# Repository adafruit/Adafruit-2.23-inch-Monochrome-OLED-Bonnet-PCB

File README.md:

## Adafruit 2.23" Monochrome OLED Bonnet for Raspberry Pi Sensor PCB

<a href="http://www.adafruit.com/products/4567"><br/>
Click here to purchase one from the Adafruit shop</a>

PCB files for the Adafruit 2.23" Monochrome OLED Bonnet for Raspberry Pi Sensor. 

Format is EagleCAD schematic and board layout
* https://www.adafruit.com/product/4567

### Description

If you're looking for a bright, readable OLED display for a [Raspberry Pi](https://www.adafruit.com/category/361) (most likely a [Pi Zero](https://www.adafruit.com/category/813)) project, this might be just the thing you need!

The **Adafruit 2.23" Monochrome OLED Bonnet for Raspberry Pi** is your chonky OLED pal, ready to snap onto any and all Raspberry Pi computers, to give you a vivid display. The Bonnet comes with a 2.13" diagonal monochrome 128x32 OLED, with sharp white pixels. The OLED the I2C pins plus GPIO #4 for reset, so you have plenty of GPIO connections available for buttons, LEDs, sensors, etc. It sits nice and flat so many cases that have an open top can have this display inserted.

[Compared to our similar PiOLED display](https://www.adafruit.com/product/3527), this OLED has the same resolution but is much larger, so it can be read from across the room. This screen is made of 128x32 individual white OLED pixels and because the display makes its own light, no backlight is required. This reduces the power required to run the OLED and is why the display has such high contrast; we really like OLED display for their crispness!

Using the display is very easy, we have a Python library for the SSD1305 chipset. Our example code allows you to draw images, text, whatever you like, using the Python imaging library. Our tests showed 30 FPS update rates so you can do animations or simple video.

**Comes completely pre-assembled and tested** so you don't need to do anything but plug it in and install our Python code! **Works with any Raspberry Pi computer that has a 2x20 connector**, such as the Pi B+, Pi 2, Pi 3, Pi 4, and Pi Zero (and any others that have a 2x20 connector!)

[On the bottom, we have a Qwiic/STEMMA QT connector for I2C sensors and devices so you can plug and play any of our STEMMA QT devices](https://www.adafruit.com/?q=stemma%20qt).

Please note that OLED displays are made of hundreds of...OLEDs! That means each pixel is a little organic LED, and if it's kept on for over 1000 hours it'll start to dim. If you want to keep the display uniformly bright, please turn off the display (set the pixels off) when it isn't needed to keep them from dimming.

### License

Adafruit invests time and resources providing this open source design, please support Adafruit and open-source hardware by purchasing products from [Adafruit](https://www.adafruit.com)!

Designed by Limor Fried/Ladyada for Adafruit Industries.

Creative Commons Attribution/Share-Alike, all text above must be included in any redistribution. 
See license.txt for additional details.

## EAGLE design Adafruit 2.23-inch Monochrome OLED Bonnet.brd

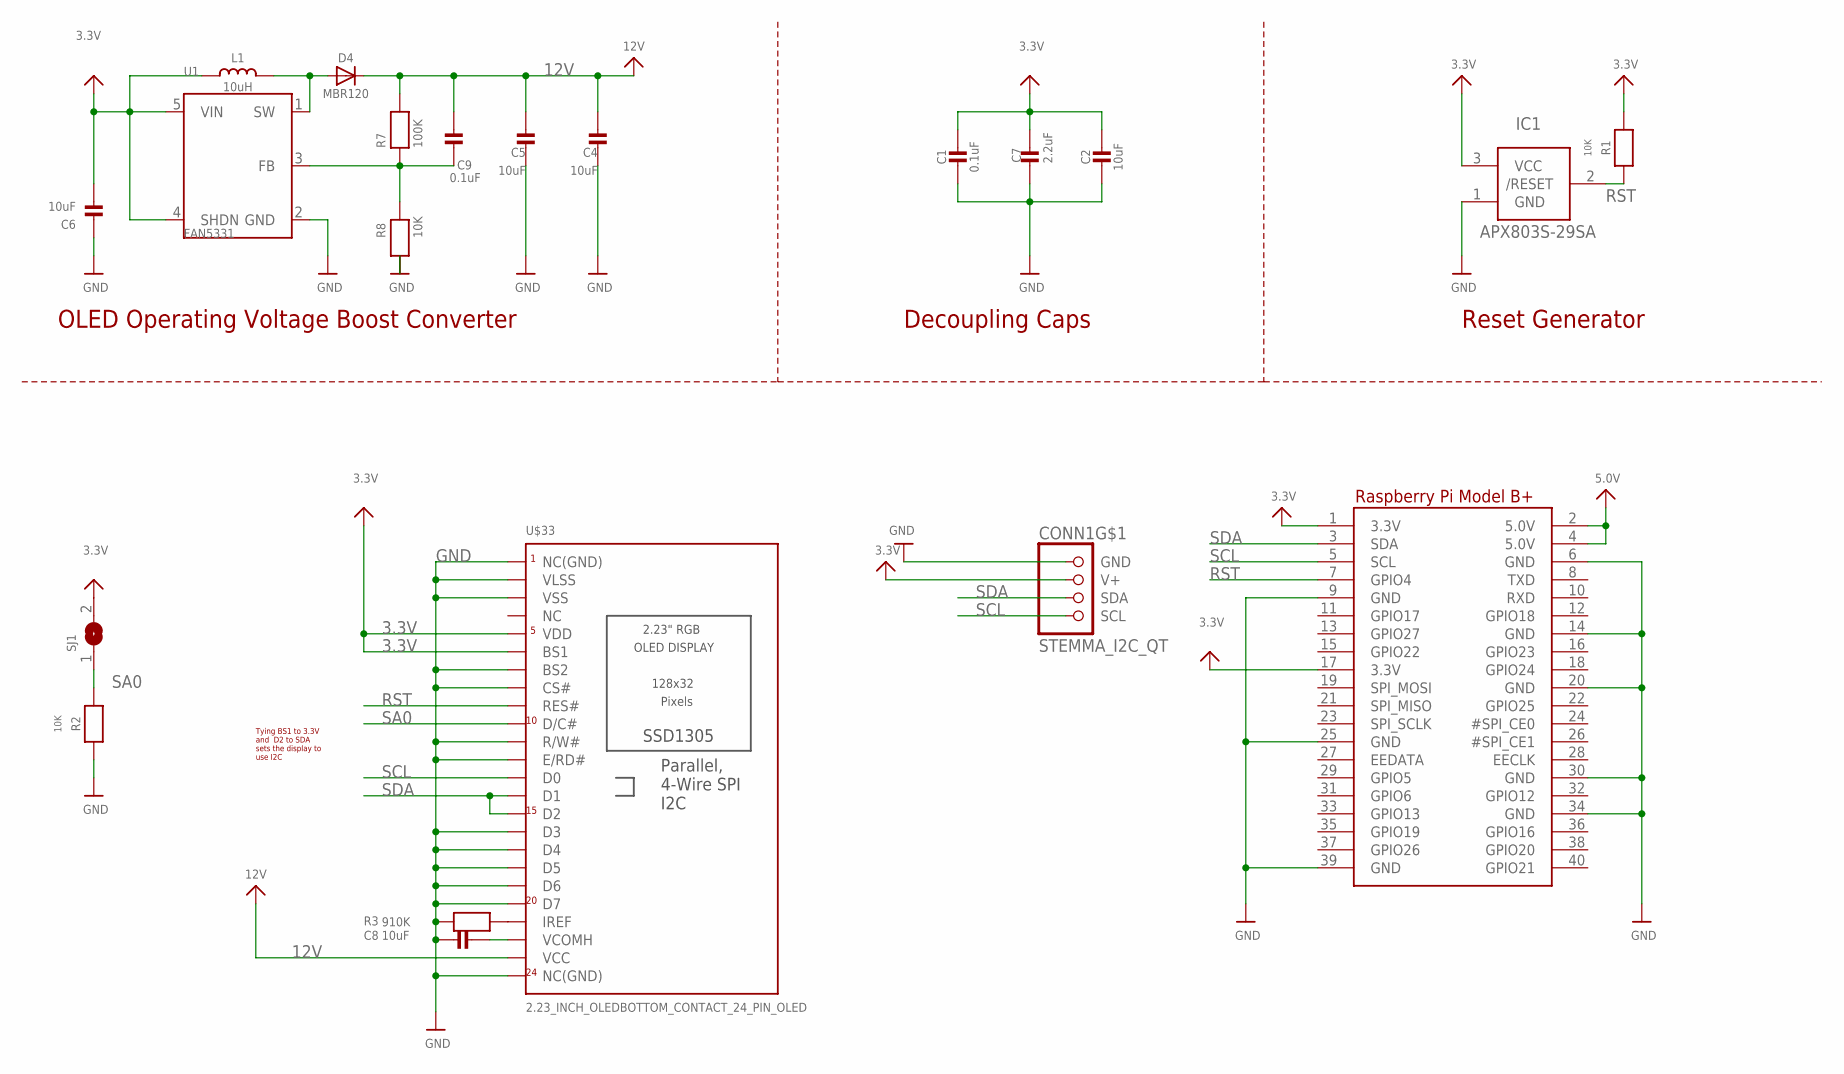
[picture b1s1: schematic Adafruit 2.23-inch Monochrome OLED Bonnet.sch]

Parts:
C1, C9: 0.1uF; 0603-NO
C2, C4, C5, C6, C8: 10uF; 0805-NO
C7: 2.2uF; 0805-NO
CONN1: STEMMA_I2C_QT; JST_SH4
D4: MBR120; SOD-123
IC1: APX803S-29SA; SOT23
L1: 10uH; INDUCTOR_1007
R1, R2, R8: 10K; 0603-NO
R3: 910K; 0805-NO
R7: 100K; 0603-NO
RPI1: RASPBERRYPI_BPLUS_BONNETSMT; PI_BONNET_SMT
SJ1: SOLDERJUMPER; SOLDERJUMPER_ARROW_NOPASTE
U1: FAN5331; SOT23-5
U$33: 2.23_INCH_OLEDBOTTOM_CONTACT_24_PIN_OLED; 2.23OLED_BOTTOM_CONTACT

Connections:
3.3V: C1.1, C2.1, C6.2, C7.2, CONN1.2 (V+), IC1.3 (VCC), L1.P$1 (1), R1.2, RPI1.1 (3.3V), RPI1.17 (3.3V), SJ1.2, U1.4 (SHDN), U1.5 (VIN), U$33.5 (VDD), U$33.6 (BS1)
5.0V: RPI1.2 (5.0V), RPI1.4 (5.0V)
12V: C4.2, C5.2, C9.1, D4.C, R7.2, U$33.23 (VCC)
GND: C1.2, C2.2, C4.1, C5.1, C6.1, C7.1, C8.1, CONN1.1 (GND), IC1.1 (GND), R2.1, R3.1, R8.1, RPI1.6 (GND), RPI1.9 (GND), RPI1.14 (GND), RPI1.20 (GND), RPI1.25 (GND), RPI1.30 (GND), RPI1.34 (GND), RPI1.39 (GND), U1.2 (GND), U$33.1 (NC(GND)), U$33.2 (VLSS), U$33.3 (VSS), U$33.7 (BS2), U$33.8 (CS#), U$33.11 (R/W#), U$33.12 (E/RD#), U$33.16 (D3), U$33.17 (D4), U$33.18 (D5), U$33.19 (D6), U$33.20 (D7), U$33.24 (NC(GND)), U$33.SPRT1 (NC(GND)), U$33.SPRT2 (NC(GND))
unnamed: R3.2, U$33.21 (IREF)
unnamed: D4.A, L1.P$2 (2), U1.1 (SW)
unnamed: C9.2, R7.1, R8.2, U1.3 (FB)
unnamed: C8.2, U$33.22 (VCOMH)
RST: IC1.2 (/RESET), R1.1, RPI1.7 (GPIO4), U$33.9 (RES#)
SA0: R2.2, SJ1.1, U$33.10 (D/C#)
SCL: CONN1.4 (SCL), RPI1.5 (SCL), U$33.13 (D0)
SDA: CONN1.3 (SDA), RPI1.3 (SDA), U$33.14 (D1), U$33.15 (D2)

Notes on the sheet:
OLED Operating Voltage Boost Converter
Tying BS1 to 3.3V and D2 to SDA sets the display to use I2C
Decoupling Caps
Reset Generator

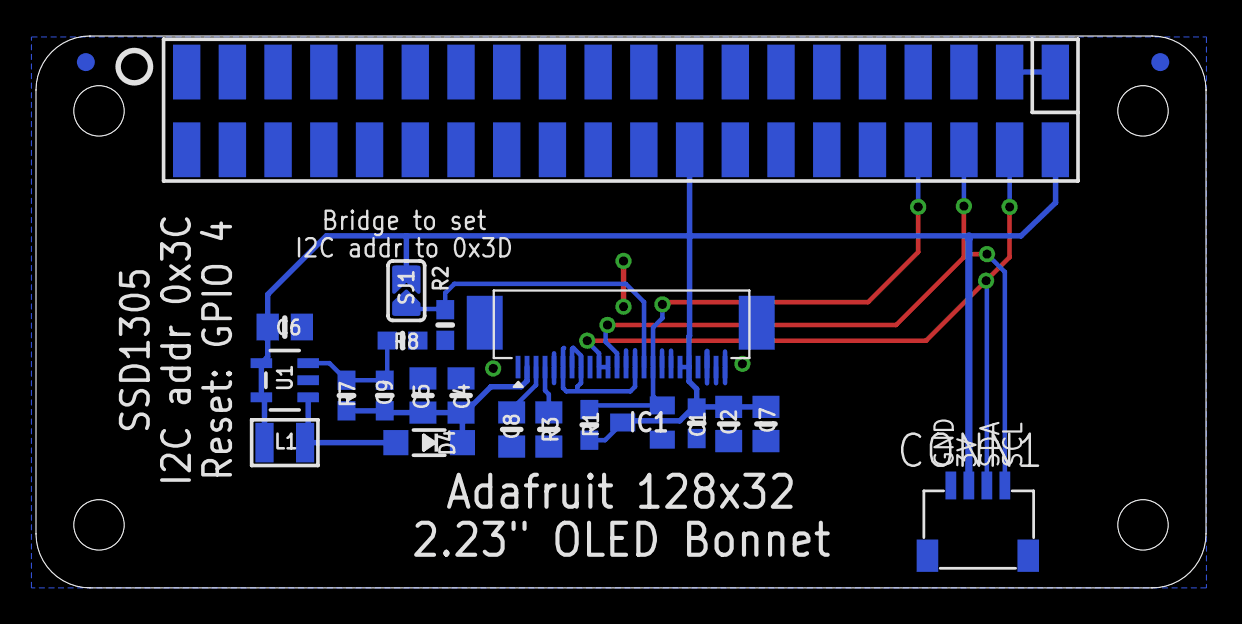
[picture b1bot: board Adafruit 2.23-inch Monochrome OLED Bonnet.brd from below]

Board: 2 copper layers, 65.0 x 30.7 mm, 23 parts (20 on the bottom side), 12 nets.

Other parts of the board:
U$2: PCBFEAT-REV-040
U$11: STEMMAQT
